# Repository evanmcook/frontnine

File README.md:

# frontnine

a small 9  button macropad that takes advantage of the castellated edges of the Elite C.

as of 2020 11 16, there is no license for this device.

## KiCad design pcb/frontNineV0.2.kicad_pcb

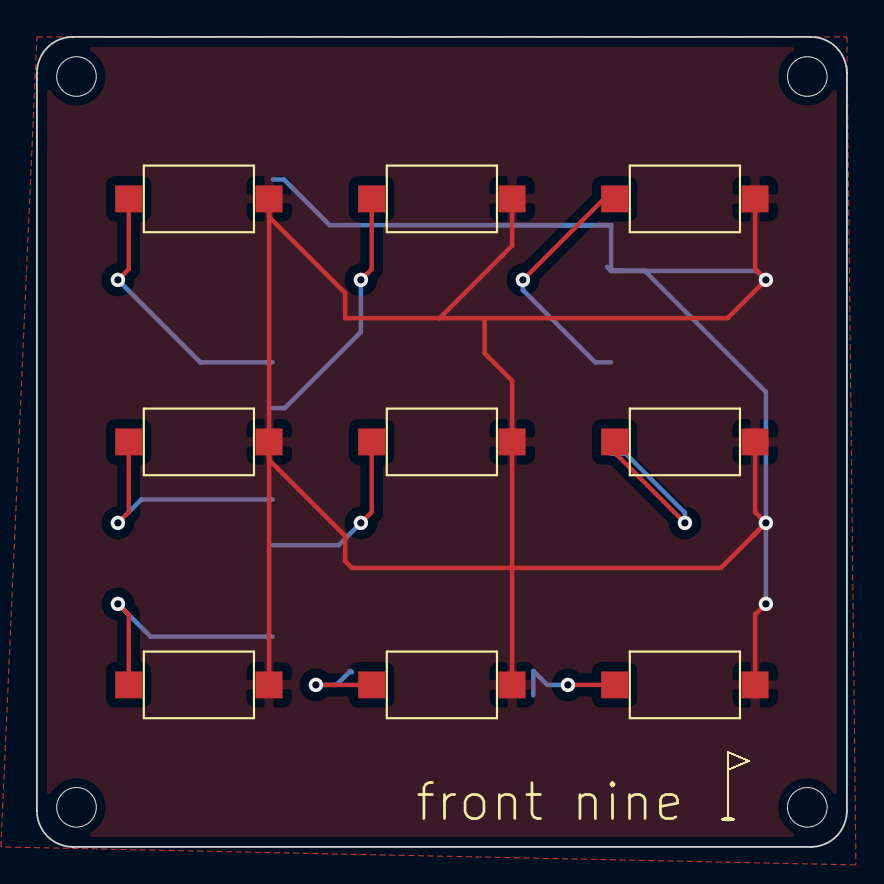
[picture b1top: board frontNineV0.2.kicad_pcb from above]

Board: 2 copper layers, 45.0 x 45.0 mm, 11 parts (1 on the bottom side), 10 nets.

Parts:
SW1, SW2, SW3, SW4, SW5, SW6, SW7, SW8, SW9: RS-282G05A3-SM_RT; SW_SPST_CK_RS282G05A3
U1: Elite-C; Elite-C-castellated-29pin
flag006bold: flag006bold

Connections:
GND: SW1.2, SW2.2, SW3.2, SW4.2, SW5.2, SW6.2, SW7.2, SW8.2, SW9.2, U1.3, U1.4, U1.23
row1: SW1.1, U1.19
row2: SW2.1, U1.18
row3: SW3.1, U1.6
row4: SW4.1, U1.16
row5: SW5.1, U1.15
row6: SW6.1, U1.8
row7: SW7.1, U1.13
row8: SW8.1, U1.29
row9: SW9.1, U1.25

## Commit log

2020-11-16 001
    file structure + first files in directories
2020-11-17 Update README.md
    image embed attempt 001
2020-11-17 Update README.md
    image attempt 002
2020-11-17 changed filenames
    no more spaces in file names
2020-11-17 Update README.md
    image attempt 003
2020-11-17 Update README.md
    changing leading structure
